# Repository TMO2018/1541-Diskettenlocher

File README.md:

# 1541-Diskettenlocher
Elektronischer Diskettenlocher mit Touch-Sensor TTP223 für das Commodore-Diskettenlaufwerk VIC-1541

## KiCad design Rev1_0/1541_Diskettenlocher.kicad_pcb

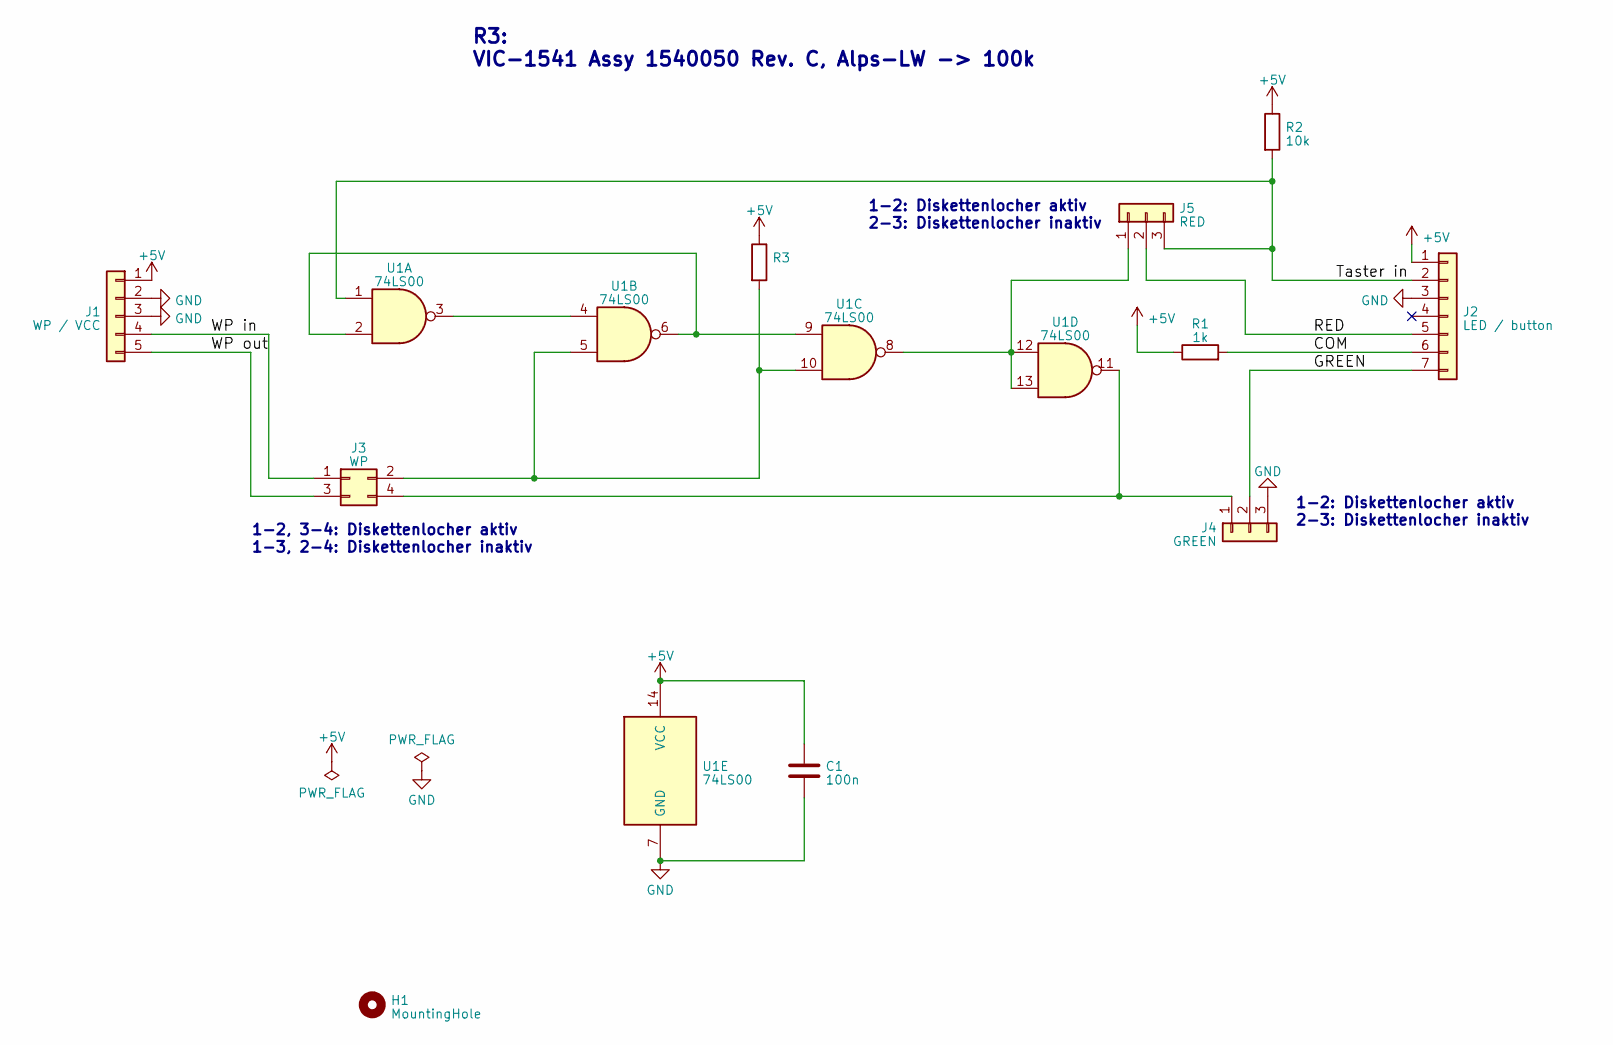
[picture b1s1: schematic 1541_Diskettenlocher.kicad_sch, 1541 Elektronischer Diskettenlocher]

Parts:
C1: 100n; C_Disc_D10.0mm_W2.5mm_P5.00mm
H1: MountingHole; MountingHole_3.2mm_M3
J1: WP / VCC; PinHeader_1x05_P2.54mm_Vertical
J2: LED / button; PinHeader_1x07_P2.54mm_Vertical
J3: WP; PinHeader_2x02_P2.54mm_Vertical
J4: GREEN; PinHeader_1x03_P2.54mm_Vertical
J5: RED; PinHeader_1x03_P2.54mm_Vertical
R1: 1k; R_Axial_DIN0207_L6.3mm_D2.5mm_P10.16mm_Horizontal
R2: 10k; R_Axial_DIN0207_L6.3mm_D2.5mm_P10.16mm_Horizontal
R3: R_Axial_DIN0207_L6.3mm_D2.5mm_P10.16mm_Horizontal
U1: 74LS00; DIP-14_W7.62mm_Socket_LongPads

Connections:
+5V: C1.1, J1.1, J2.1, R1.1, R2.1, R3.1, U1.14 (VCC)
/COM: J2.6, R1.2
/GREEN: J2.7, J4.2
/RED: J2.5, J5.2
/Taster in: J2.2, J5.3, R2.2, U1.1
/WP in: J1.4, J3.1
/WP out: J1.5, J3.3
GND: C1.2, J1.2, J1.3, J2.3, J4.3, U1.7 (GND)
unnamed: J3.2, R3.2, U1.5, U1.10
unnamed: J3.4, J4.1, U1.11
unnamed: J5.1, U1.8, U1.12, U1.13
unnamed: U1.2, U1.6, U1.9
unnamed: U1.3, U1.4

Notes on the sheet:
1-2: Diskettenlocher aktiv 2-3: Diskettenlocher inaktiv
R3: VIC-1541 Assy 1540050 Rev. C, Alps-LW -> 100k
1-2, 3-4: Diskettenlocher aktiv 1-3, 2-4: Diskettenlocher inaktiv

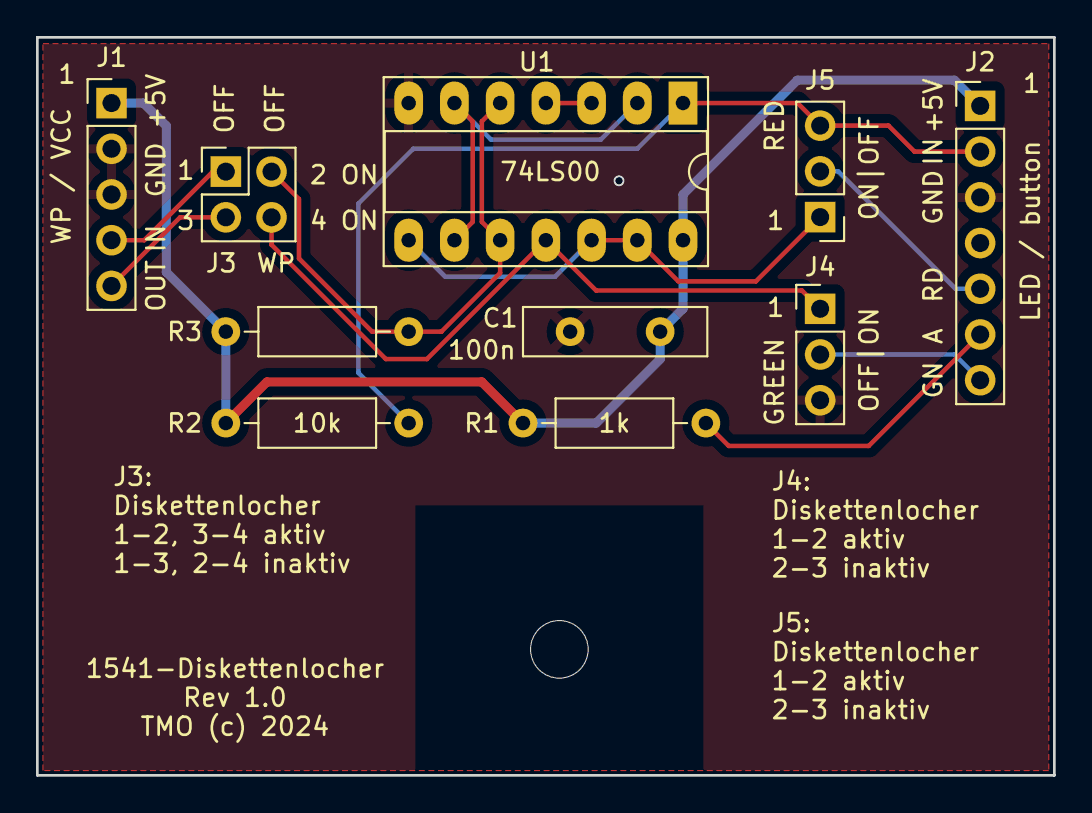
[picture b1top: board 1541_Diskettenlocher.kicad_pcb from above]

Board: 2 copper layers, 56.5 x 41.0 mm, 11 parts (0 on the bottom side), 13 nets.

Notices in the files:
Rev1_0/1541_Diskettenlocher.kicad_pcb:
TMO (c) 2024
